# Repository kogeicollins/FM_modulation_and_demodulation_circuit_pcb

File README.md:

# FM_modulation_and_demodulation_circuit_pcb
 fm moddemod design

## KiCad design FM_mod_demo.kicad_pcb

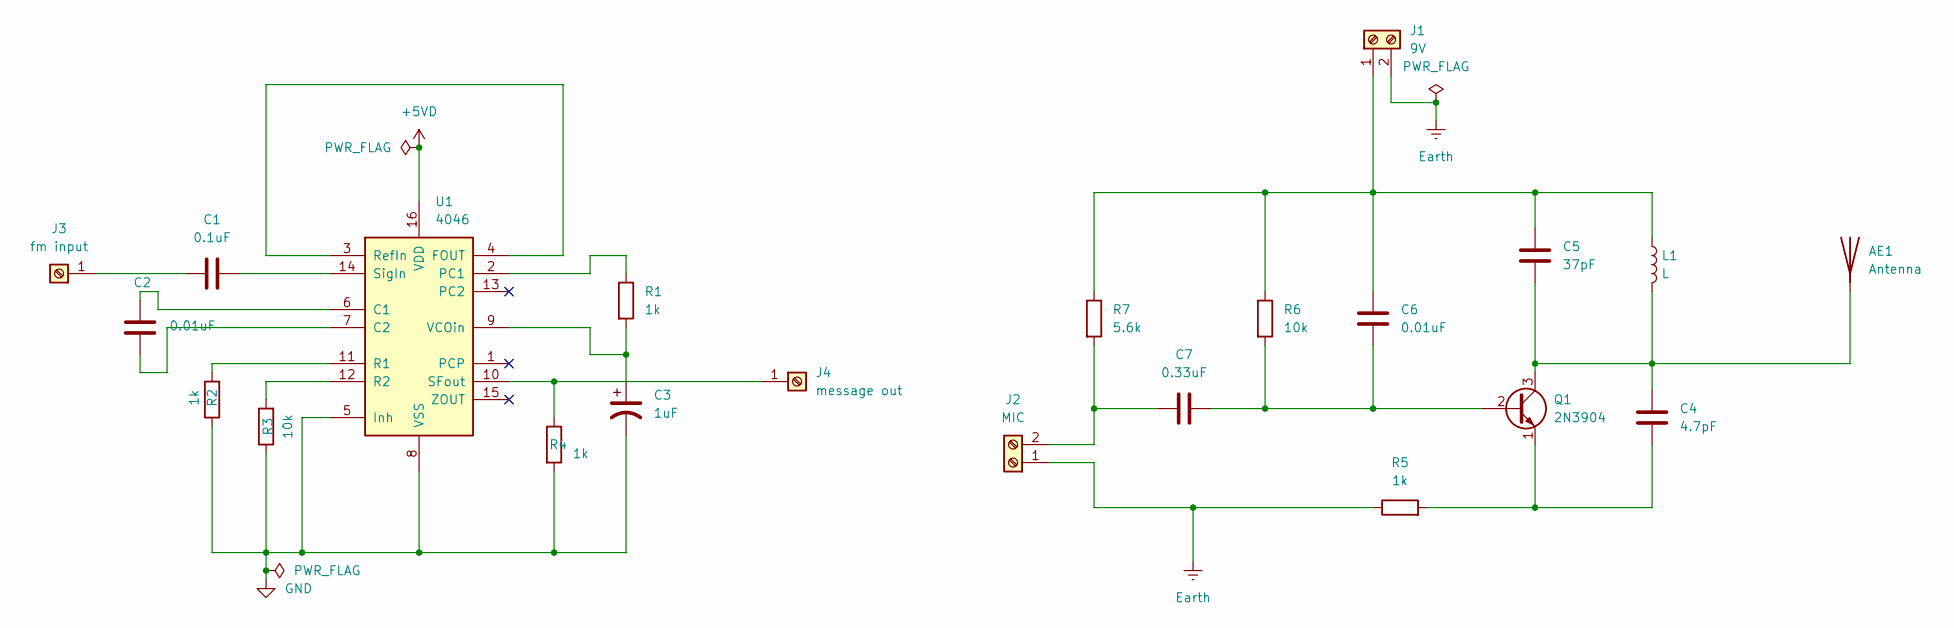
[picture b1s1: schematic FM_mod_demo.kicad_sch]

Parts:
AE1: Antenna; Texas_SWRA117D_2.4GHz_Left
C1: 0.1uF; C_0201_0603Metric
C2, C6: 0.01uF; C_0201_0603Metric
C3: 1uF; CP_Elec_3x5.3
C4: 4.7pF; C_0201_0603Metric
C5: 37pF; C_0201_0603Metric
C7: 0.33uF; C_0201_0603Metric
J1: 9V; TerminalBlock_MetzConnect_Type055_RT01502HDWU_1x02_P5.00mm_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
J2: MIC; TerminalBlock_MetzConnect_Type055_RT01502HDWU_1x02_P5.00mm_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
J3: fm input; TerminalBlock_MetzConnect_360272_1x01_Horizontal_ScrewM2.6
J4: message out; TerminalBlock_MetzConnect_360272_1x01_Horizontal_ScrewM2.6
L1: L; L_0201_0603Metric
Q1: 2N3904; TO-92_Inline
R1, R2, R4, R5: 1k; R_0201_0603Metric
R3, R6: 10k; R_0201_0603Metric
R7: 5.6k; R_0201_0603Metric
U1: 4046; DIP-16_W7.62mm

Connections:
+5VD: U1.16 (VDD)
Earth: J1.2, J2.1, R5.1
GND: C3.2, R2.1, R3.1, R4.2, U1.5 (Inh), U1.8 (VSS)
unnamed: AE1.1 (A), C4.1, C5.2, L1.2, Q1.3 (C)
unnamed: C5.1, C6.1, J1.1, L1.1, R6.1, R7.1
unnamed: C7.1, J2.2, R7.2
unnamed: C1.1, J3.1
unnamed: J4.1, R4.1, U1.10 (SFout)
unnamed: C6.2, C7.2, Q1.2 (B), R6.2
unnamed: C4.2, Q1.1 (E), R5.2
unnamed: C2.1, U1.6 (C1)
unnamed: C2.2, U1.7 (C2)
unnamed: U1.3 (RefIn), U1.4 (FOUT)
unnamed: R1.1, U1.2 (PC1)
unnamed: R2.2, U1.11 (R1)
unnamed: R3.2, U1.12 (R2)
unnamed: C1.2, U1.14 (SigIn)
unnamed: C3.1, R1.2, U1.9 (VCOin)

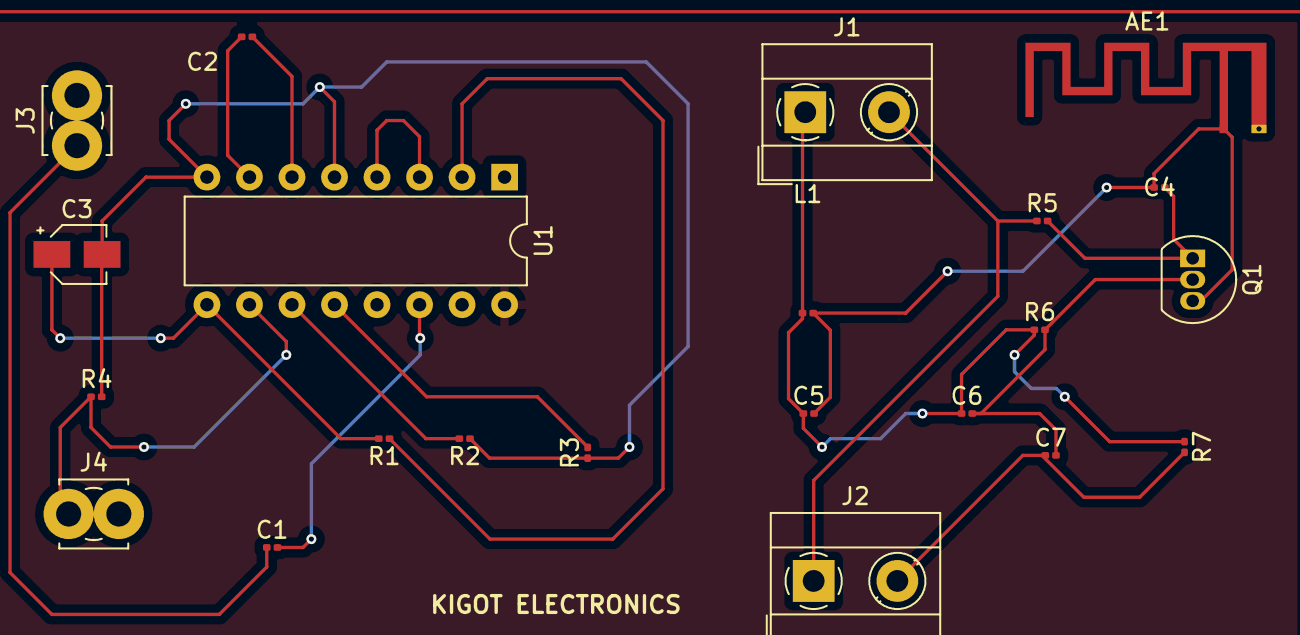
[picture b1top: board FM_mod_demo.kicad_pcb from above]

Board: 2 copper layers, 22 parts (0 on the bottom side), 17 nets.

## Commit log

2024-11-27 the kicad files
    fm moddemod files
